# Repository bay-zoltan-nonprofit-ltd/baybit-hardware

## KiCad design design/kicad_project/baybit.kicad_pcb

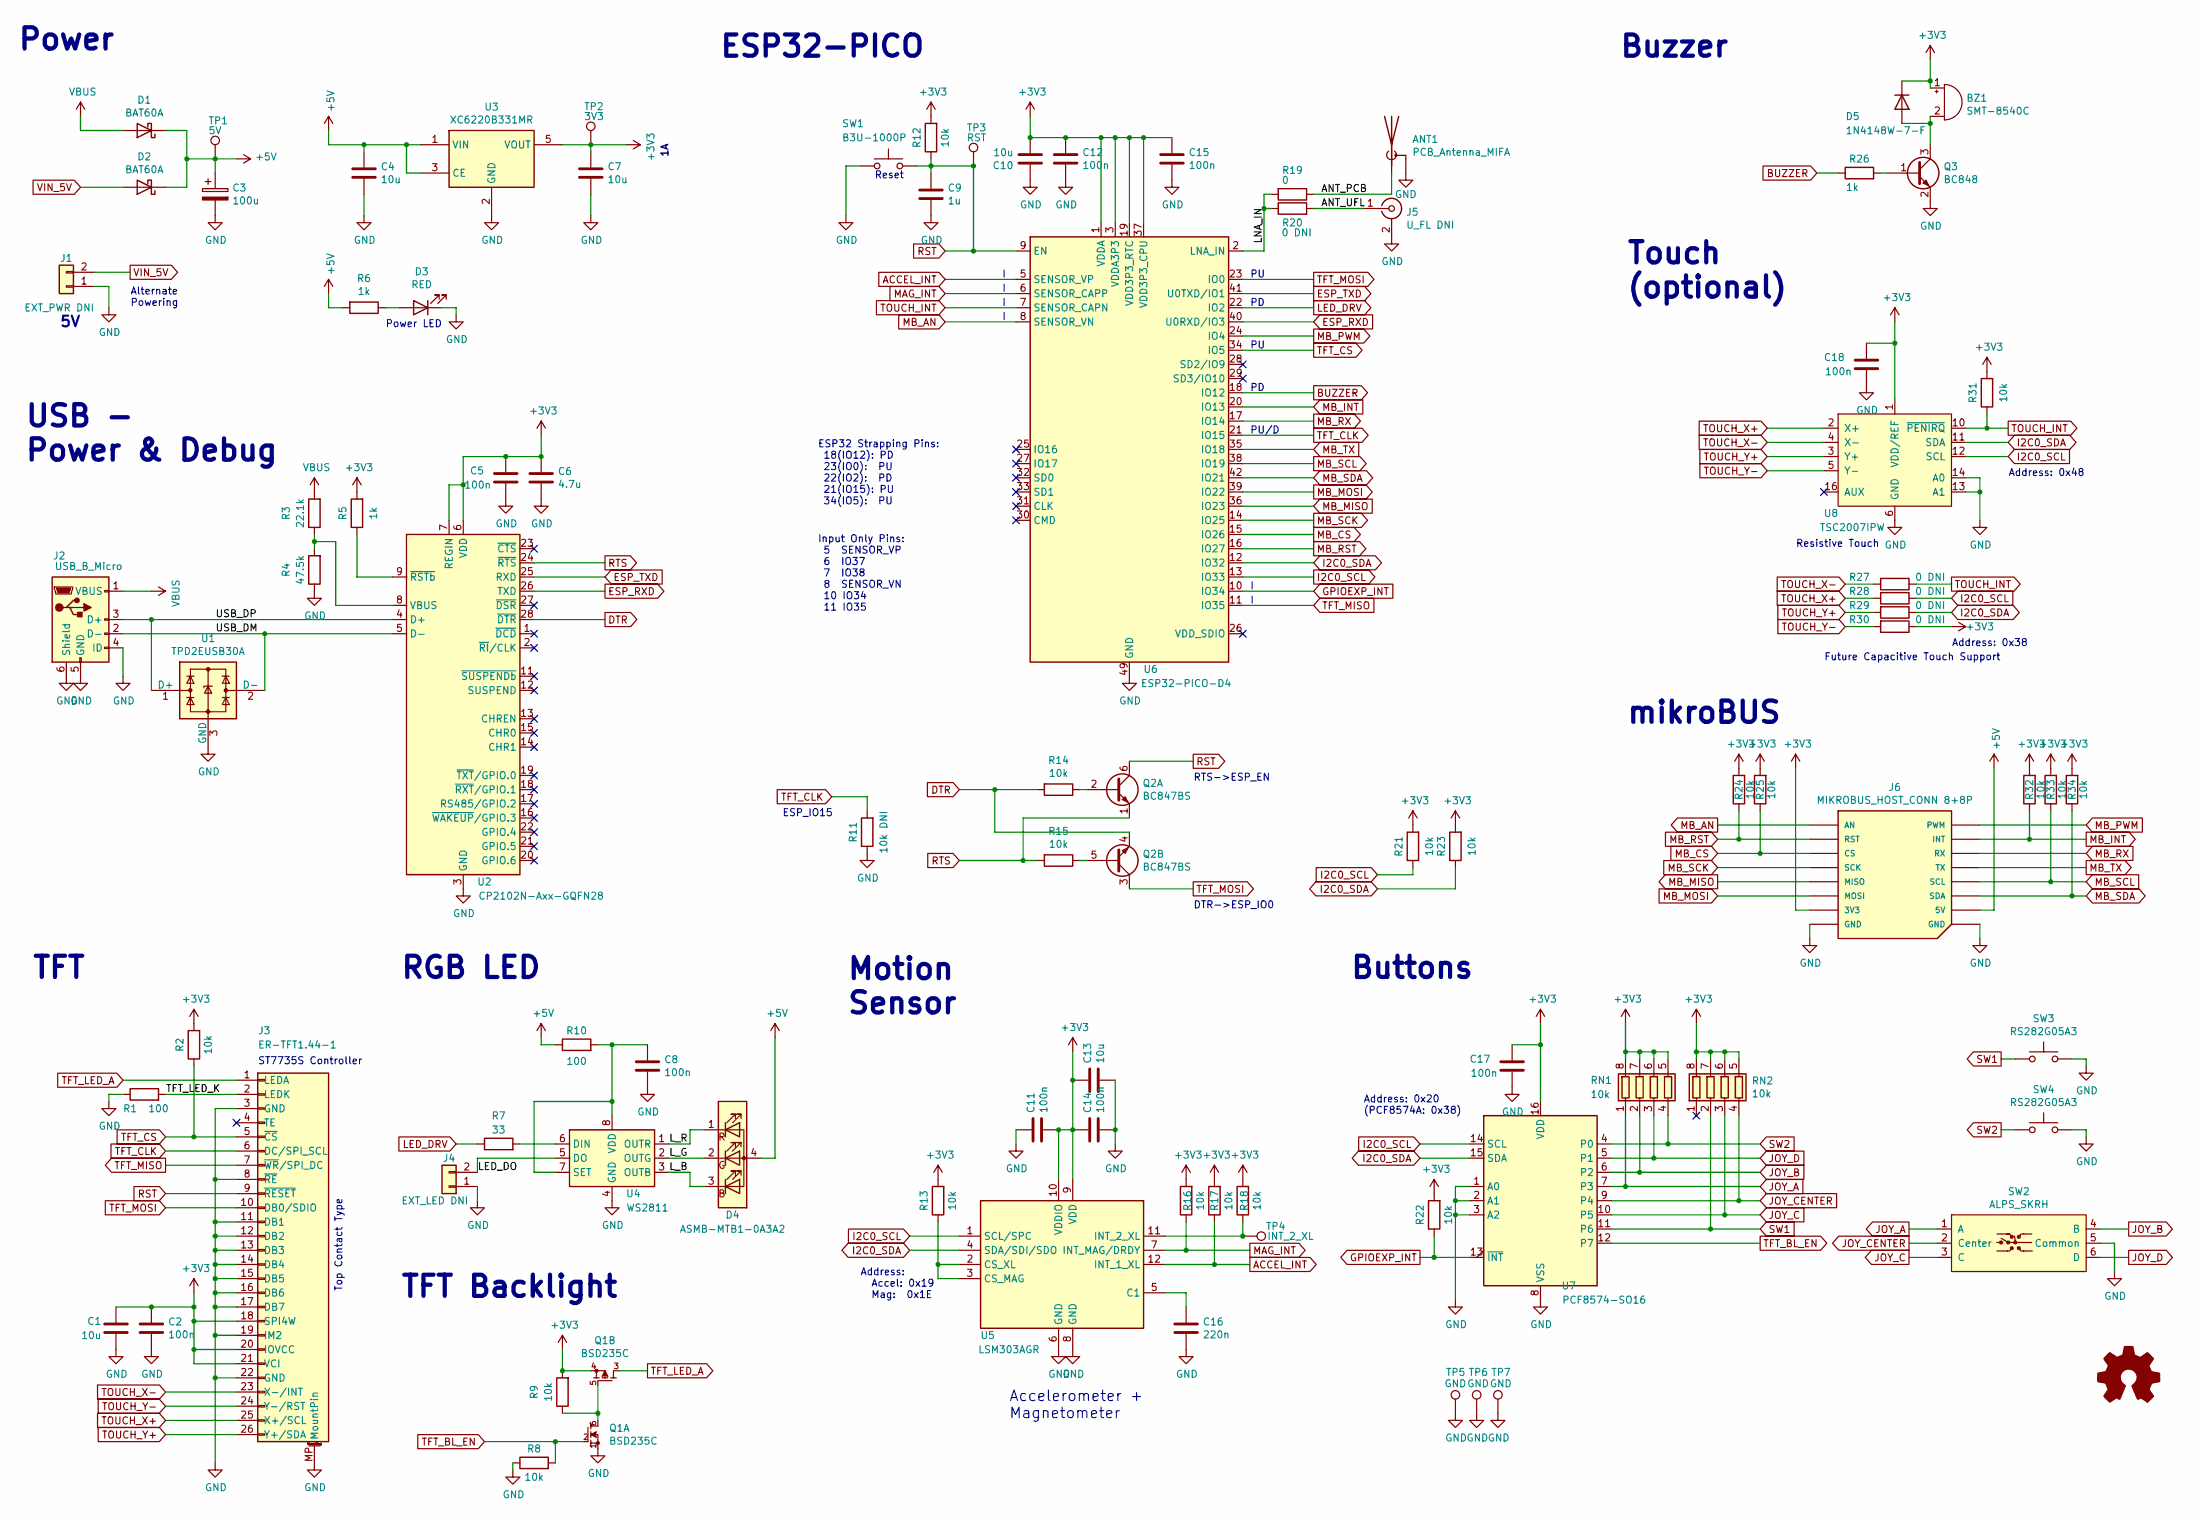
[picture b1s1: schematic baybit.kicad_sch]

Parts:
ANT1: PCB_Antenna_MIFA; Texas_SWRA117D_2.4GHz_Left
BZ1: SMT-8540C; BUZZER_SMT_85X85X32
C1, C4, C7, C10, C13: 10u; C_0603_1608Metric
C2, C5, C8, C11, C12, C14, C15, C17, C18: 100n; C_0402_1005Metric
C3: 100u; CP_EIA-3528-21_Kemet-B
C6: 4.7u; C_0603_1608Metric
C9: 1u; C_0402_1005Metric
C16: 220n; C_0402_1005Metric
D1, D2: BAT60A; D_SOD-323
D3: RED; LED_0603_1608Metric
D4: ASMB-MTB1-0A3A2; LED_Avago_PLCC4_3.2x2.8mm_CW
D5: 1N4148W-7-F; D_SOD-123
J1: EXT_PWR DNI; PinHeader_1x02_P2.54mm_Vertical
J2: USB_B_Micro; USB_Micro-B_Molex-105017-0001
J3: ER-TFT1.44-1; Hirose_FH12A-26S-0.5SH_1x26-1MP_P0.50mm_Horizontal
J4: EXT_LED DNI; PinHeader_1x02_P2.54mm_Vertical
J5: U_FL DNI; U.FL_Hirose_U.FL-R-SMT-1_Vertical
J6: MIKROBUS_HOST_CONN 8+8P; MIKROBUS_HOST_CONN
Q1: BSD235C; SOT-363_SC-70-6
Q2: BC847BS; SOT-363_SC-70-6
Q3: BC848; SOT-23
R1, R10: 100; R_0603_1608Metric
R2, R8, R9, R12, R13, R14, R15, R16, R17, R18, R21, R22, R23, R24, R25, R31, R32, R33, R34: 10k; R_0402_1005Metric
R3: 22.1k; R_0402_1005Metric
R4: 47.5k; R_0402_1005Metric
R5, R6, R26: 1k; R_0402_1005Metric
R7: 33; R_0402_1005Metric
R11: 10k DNI; R_0402_1005Metric
R19: 0; R_0402_1005Metric
R20, R27, R28, R29, R30: 0 DNI; R_0402_1005Metric
RN1, RN2: 10k; R_Array_Convex_4x0603
SW1: B3U-1000P; SW_SPST_B3U-1000P
SW2: ALPS_SKRH
SW3, SW4: RS282G05A3; SW_SPST_CK_RS282G05A3
TP1: 5V; TestPoint_Pad_D1.0mm
TP2: 3V3; TestPoint_Pad_D1.0mm
TP3: RST; TestPoint_Pad_D1.0mm
TP4: INT_2_XL; TestPoint_Pad_D1.0mm
TP5, TP6, TP7: GND; TestPoint_THTPad_D2.0mm_Drill1.0mm
U1: TPD2EUSB30A; Texas_DRT-3
U2: CP2102N-Axx-GQFN28; QFN-28-1EP_5x5mm_P0.5mm_EP3.35x3.35mm
U3: XC6220B331MR; SOT-23-5
U4: WS2811; SOIC-8_3.9x4.9mm_P1.27mm
U5: LSM303AGR; LGA-12_2x2mm_P0.5mm
U6: ESP32-PICO-D4; QFN-48-1EP_7x7mm_P0.5mm_EP5.15x5.15mm
U7: PCF8574-SO16; SOIC-16W_7.5x10.3mm_P1.27mm
U8: TSC2007IPW; TSSOP-16_4.4x5mm_P0.65mm

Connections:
+3V3: BZ1.1 (-), C1.2, C2.1, C5.2, C6.1, C7.1, C10.2, C11.2, C12.1, C13.1, C14.1, C15.1, C17.2, C18.2, D5.1 (K), J3.18 (SPI4W), J3.20 (IOVCC), J3.21 (VCI), J6.P7 (3V3), Q1.4 (S), R2.2, R5.2, R9.2, R12.2, R13.2, R16.2, R17.2, R18.2, R21.2, R22.2, R23.2, R24.2, R25.2, R30.1, R31.2, R32.2, R33.2, R34.2, RN1.5 (R4.2), RN1.6 (R3.2), RN1.7 (R2.2), RN1.8 (R1.2), RN2.5 (R4.2), RN2.6 (R3.2), RN2.7 (R2.2), RN2.8 (R1.2), TP2.1, U2.6 (VDD), U2.7 (REGIN), U3.5 (VOUT), U5.9 (VDD), U5.10 (VDDIO), U6.1 (VDDA), U6.3 (VDDA3P3), U6.4 (VDDA3P3), U6.19 (VDD3P3_RTC), U6.37 (VDD3P3_CPU), U6.43 (VDDA), U6.46 (VDDA), U7.16 (VDD), U8.1 (VDD/REF); also elsewhere on the board
+5V: C3.1, C4.1, D1.1 (K), D2.1 (K), D4.4 (A), J6.P10 (5V), R6.2, R10.1, TP1.1, U3.1 (VIN), U3.3 (CE)
/ANT_PCB: ANT1.1 (A), R19.1
/ANT_UFL: J5.1 (In), R20.2
/LED_DO: J4.2, U4.5 (DO)
/LNA_IN: R19.2, R20.1, U6.2 (LNA_IN)
/L_B: D4.3 (BK), U4.3 (OUTB)
/L_G: D4.2 (GK), U4.2 (OUTG)
/L_R: D4.1 (RK), U4.1 (OUTR)
/TFT_LED_K: J3.2 (LEDK), R1.2
/USB_DM: J2.2 (D-), U1.2 (D-), U2.5 (D-)
/USB_DP: J2.3 (D+), U1.1 (D+), U2.4 (D+)
ACCEL_INT: R17.1, U5.12 (INT_1_XL), U6.5 (SENSOR_VP)
BUZZER: R26.1, U6.18 (IO12)
DTR: Q2.4 (E2), R14.2, U2.28 (~DTR)
ESP_RXD: U2.26 (TXD), U6.40 (U0RXD/IO3)
ESP_TXD: U2.25 (RXD), U6.41 (U0TXD/IO1)
GND: ANT1.2 (Shield), C1.1, C2.2, C3.2, C4.2, C5.1, C6.2, C7.2, C8.2, C9.2, C10.1, C11.1, C12.2, C13.2, C14.2, C15.2, C16.2, C17.1, C18.1, D3.1 (K), J1.1, J2.4 (ID), J2.5 (GND), J2.6 (Shield), J3.3 (GND), J3.8 (~RE), J3.11 (DB1), J3.12 (DB2), J3.13 (DB3), J3.14 (DB4), J3.15 (DB5), J3.16 (DB6), J3.17 (DB7), J3.19 (IM2), J3.22 (GND), J3.MP (MountPin), J4.1, J5.2 (Ext), J6.P8 (GND), J6.P9 (GND), Q1.1 (S), Q3.2 (E), R1.1, R4.1, R8.1, R11.1, SW1.1, SW2.5 (Common), SW3.2, SW4.2, TP5.1, TP6.1, TP7.1, U1.3 (GND), U2.3 (GND), U2.29 (GND), U3.2 (GND), U4.4 (GND), U5.6 (GND), U5.8 (GND), U6.49 (GND), U7.1 (A0), U7.2 (A1), U7.3 (A2), U7.8 (VSS), U8.6 (GND), U8.13 (A1), U8.14 (A0)
GPIOEXP_INT: R22.1, U6.10 (IO34), U7.13 (~INT)
I2C0_SCL: R21.1, R28.1, U5.1 (SCL/SPC), U6.13 (IO33), U7.14 (SCL), U8.12 (SCL)
I2C0_SDA: R23.1, R29.1, U5.4 (SDA/SDI/SDO), U6.12 (IO32), U7.15 (SDA), U8.11 (SDA)
JOY_A: RN1.1 (R1.1), SW2.1 (A), U7.7 (P3)
JOY_B: RN1.2 (R2.1), SW2.4 (B), U7.6 (P2)
JOY_C: RN2.3 (R3.1), SW2.3 (C), U7.10 (P5)
JOY_CENTER: RN2.4 (R4.1), SW2.2 (Center), U7.9 (P4)
JOY_D: RN1.3 (R3.1), SW2.6 (D), U7.5 (P1)
LED_DRV: R7.1, U6.22 (IO2)
MAG_INT: R16.1, U5.7 (INT_MAG/DRDY), U6.6 (SENSOR_CAPP)
MB_AN: J6.P1 (AN), U6.8 (SENSOR_VN)
MB_CS: J6.P3 (CS), R25.1, U6.15 (IO26)
MB_INT: J6.P15 (INT), R32.1, U6.20 (IO13)
MB_MISO: J6.P5 (MISO), U6.36 (IO23)
MB_MOSI: J6.P6 (MOSI), U6.39 (IO22)
MB_PWM: J6.P16 (PWM), U6.24 (IO4)
MB_RST: J6.P2 (RST), R24.1, U6.16 (IO27)
MB_RX: J6.P14 (RX), U6.17 (IO14)
MB_SCK: J6.P4 (SCK), U6.14 (IO25)
MB_SCL: J6.P12 (SCL), R33.1, U6.38 (IO19)
MB_SDA: J6.P11 (SDA), R34.1, U6.42 (IO21)
MB_TX: J6.P13 (TX), U6.35 (IO18)
unnamed: BZ1.2 (+), D5.2 (A), Q3.3 (C)
unnamed: D3.2 (A), R6.1
unnamed: Q1.5 (G), Q1.6 (D), R9.1
unnamed: Q2.2 (B1), R14.1
unnamed: Q2.5 (B2), R15.1
unnamed: Q3.1 (B), R26.2
unnamed: R3.1, R4.2, U2.8 (VBUS)
unnamed: R5.1, U2.9 (~RSTb)
unnamed: R7.2, U4.6 (DIN)
unnamed: C8.1, R10.2, U4.7 (SET), U4.8 (VDD)
unnamed: C16.1, U5.5 (C1)
unnamed: R13.1, U5.2 (CS_XL), U5.3 (CS_MAG)
unnamed: R18.1, TP4.1, U5.11 (INT_2_XL)
RST: C9.1, J3.9 (~RESET), Q2.6 (C1), R12.1, SW1.2, TP3.1, U6.9 (EN)
RTS: Q2.1 (E1), R15.2, U2.24 (~RTS)
SW1: RN2.2 (R2.1), SW3.1, U7.11 (P6)
SW2: RN1.4 (R4.1), SW4.1, U7.4 (P0)
TFT_BL_EN: Q1.2 (G), R8.2, U7.12 (P7)
TFT_CLK: J3.6 (DC/SPI_SCL), R11.2, U6.21 (IO15)
TFT_CS: J3.5 (~CS), R2.1, U6.34 (IO5)
TFT_LED_A: J3.1 (LEDA), Q1.3 (D)
TFT_MISO: J3.7 (~WR/SPI_DC), U6.11 (IO35)
TFT_MOSI: J3.10 (DB0/SDIO), Q2.3 (C2), U6.23 (IO0); also elsewhere on the board
TOUCH_INT: R27.1, R31.1, U6.7 (SENSOR_CAPN), U8.10 (~PENIRQ)
TOUCH_X+: J3.25 (X+/SCL), R28.2, U8.2 (X+)
TOUCH_X-: J3.23 (X-/INT), R27.2, U8.4 (X-)
TOUCH_Y+: J3.26 (Y+/SDA), R29.2, U8.3 (Y+)
TOUCH_Y-: J3.24 (Y-/RST), R30.2, U8.5 (Y-)
VBUS: D1.2 (A), J2.1 (VBUS), R3.2
VIN_5V: D2.2 (A), J1.2

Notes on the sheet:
ESP32 Strapping Pins: 18(IO12): PD 23(IO0): PU 22(IO2): PD 21(IO15): PU 34(IO5): PU
Touch (optional)
Future Capacitive Touch Support
Address: 0x20 (PCF8574A: 0x38)
Buttons
Buzzer
RTS->ESP_EN
ESP32-PICO
Input Only Pins: 5 SENSOR_VP 6 IO37 7 IO38 8 SENSOR_VN 10 IO34 11 IO35
Address: Accel: 0x19 Mag: 0x1E
USB - Power & Debug
TFT Backlight
TFT
Power
Reset
PU/D
Address: 0x38
Alternate Powering
ST7735S Controller
mikroBUS
RGB LED
Motion Sensor
Resistive Touch
Power LED
Top Contact Type
ESP_IO15
Accelerometer + Magnetometer
DTR->ESP_IO0
Address: 0x48

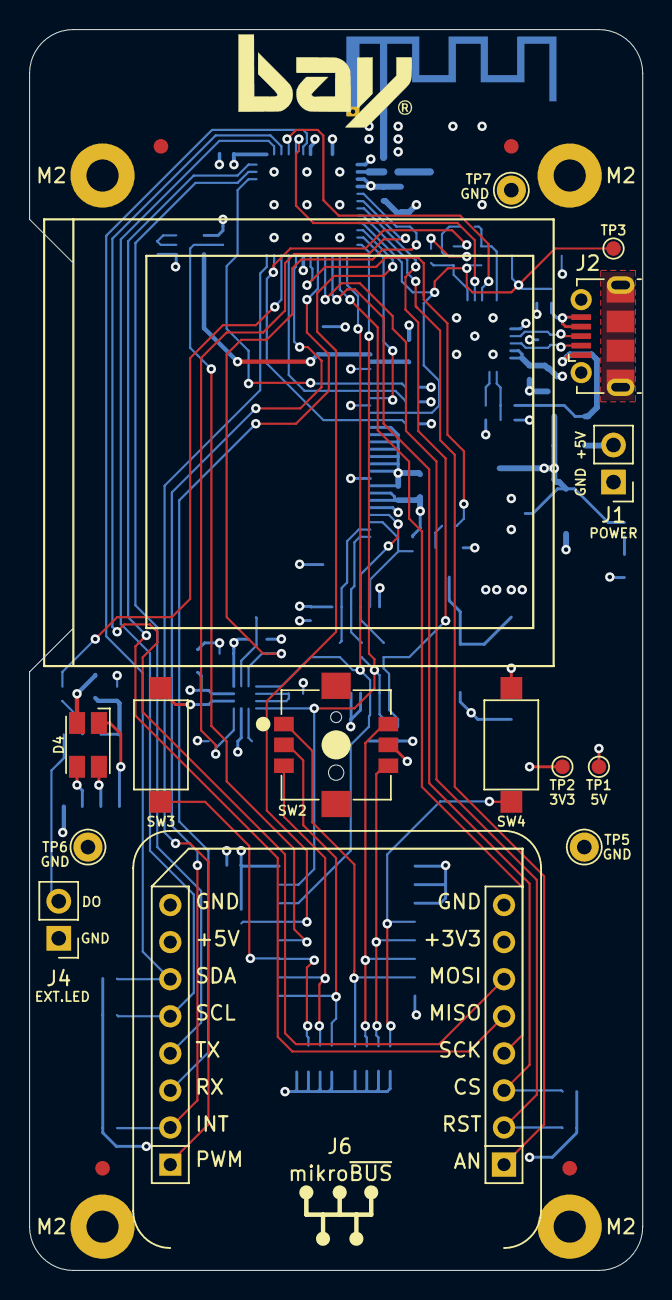
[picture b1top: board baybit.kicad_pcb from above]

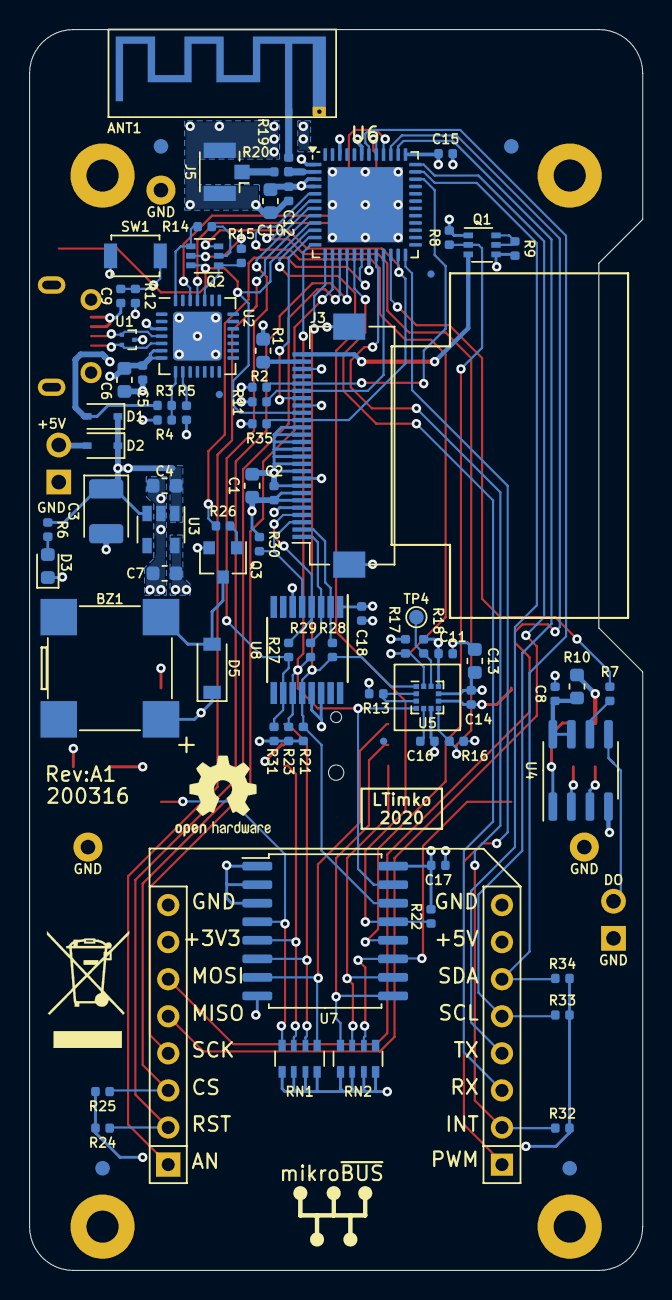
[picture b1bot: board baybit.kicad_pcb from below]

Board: 4 copper layers, 42.0 x 85.0 mm, 90 parts (76 on the bottom side), 70 nets.

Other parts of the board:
R35: 10k; R_0402_1005Metric

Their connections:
+3V3: R35.2; also elsewhere on the board
TFT_MOSI: R35.1; also elsewhere on the board

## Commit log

2020-03-06 Import project
2022-01-05 Migrated to Kicad 6
2025-02-21 Migrated to Kicad 9
